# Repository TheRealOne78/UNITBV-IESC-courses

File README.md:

# UNITBV-IESC-courses

## ROMÂNĂ / ROMANIAN

Acest depozit git servește drept caietul meu digital personal pentru toate orele pe care le-am urmat la facultatea de _Inginerie Electrică și Știința Calculatoarelor_ din UniTBv (Universitatea Transilvania din Brașov). Chiar dacă vizibilitatea acestui depozit este setată la vizualizare publică (acces mai ușor pentru mine), toate fișierele și conținutul lor sunt protejate în mare măsură de drepturi de autor fie de către UniTBv sau de către alți terți care pot avea sau nu o relație cu UniTBv.

Cu toate acestea, bibliografia este disponibilă pe fiecare fișier `README.md` pentru fiecare clasă, așa cum este furnizată de UniTBv. Dacă sunteți deținătorul drepturilor de autor și nu puteți găsi creditele necesare în secțiunile de bibliografie, vă rog să-mi trimiteți un E-Mail la <a href="elias.bajcsi@student.unitbv.ro">elias.bajcsi@student.unitbv.ro</a> deoarece toate _Pull requests_ și _Issues_ vor fi ignorate.

## ENGLEZĂ / ENGLISH

This git repository serves as my personal digital notebook for all classes I attended to the _Electrical Engineering and Computer Science_ college at UniTBv (Transilvania University of Brașov). Even though this repository's visibility is set to public view (easier access for myself), all the files and their contents are heavily copyrighted either by UniTBv or third parties that may or may not have a relation with UniTBv.

However, bibliography is available on every `README.md` file for every class, as provided by UniTBv. If you are a copyright holder and you can't find the necessary credits in the bibliography sections, please send me an E-Mail to <a href="elias.bajcsi@student.unitbv.ro">elias.bajcsi@student.unitbv.ro</a> as all _Pull requests_ and _Issues_ will be ignored.

### Grupa/Group: 4LF731

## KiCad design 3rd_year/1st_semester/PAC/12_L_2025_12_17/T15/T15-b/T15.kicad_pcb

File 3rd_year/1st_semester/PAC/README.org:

#+TITLE: Proiectarea asistată de calculator a modulelor electronice [PAC]

Profesor de curs: PANĂ Gheorghe
Profesor de laborator: PANĂ Gheorghe

An III, 2025-2026 Semestrul I

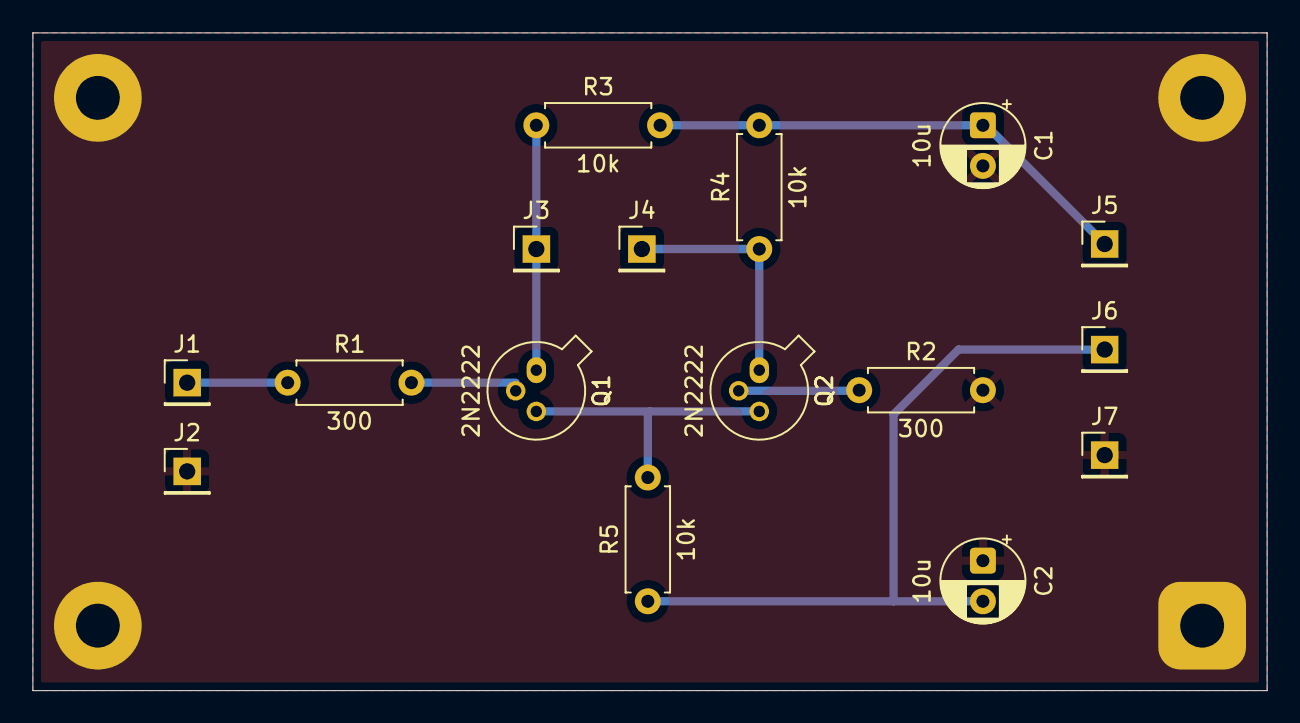
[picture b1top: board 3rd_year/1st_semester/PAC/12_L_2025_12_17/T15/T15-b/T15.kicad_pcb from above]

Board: 2 copper layers, 76.0 x 40.5 mm, 20 parts (0 on the bottom side), 9 nets.

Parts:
C1, C2: 10u; CP_Radial_D5.0mm_P2.50mm
J1, J2, J3, J4, J5, J6, J7: Conn_01x01; PinHeader_1x01_P2.54mm_Vertical
Q1, Q2: 2N2222; TO-18-3
R1, R2: 300; R_Axial_DIN0207_L6.3mm_D2.5mm_P7.62mm_Horizontal
R3, R4, R5: 10k; R_Axial_DIN0207_L6.3mm_D2.5mm_P7.62mm_Horizontal
REF1, REF2, REF3, REF4: MountingHole_2.7mm_Pad

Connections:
0: C1.2, C2.1, J2.1, J7.1, R2.2, REF1.1, REF2.1, REF3.1, REF4.1
/V+: C1.1, J5.1, R3.2, R4.2
/V-: C2.2, J6.1, R5.1
/out1: J3.1, Q1.1 (C), R3.1
/out2: J4.1, Q2.1 (C), R4.1
unnamed: J1.1, R1.1
unnamed: Q1.2 (B), R1.2
unnamed: Q1.3 (E), Q2.3 (E), R5.2
unnamed: Q2.2 (B), R2.1

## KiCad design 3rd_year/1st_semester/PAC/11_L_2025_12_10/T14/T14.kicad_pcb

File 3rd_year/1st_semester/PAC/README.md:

## PAC - Proiectarea Asistată de Calculator a modulelor electronice

Profesor de curs:
Profesor de seminar:
Profesor de laborator:
Profesor de proiect:

An III, 2025-2026 Semestrul I

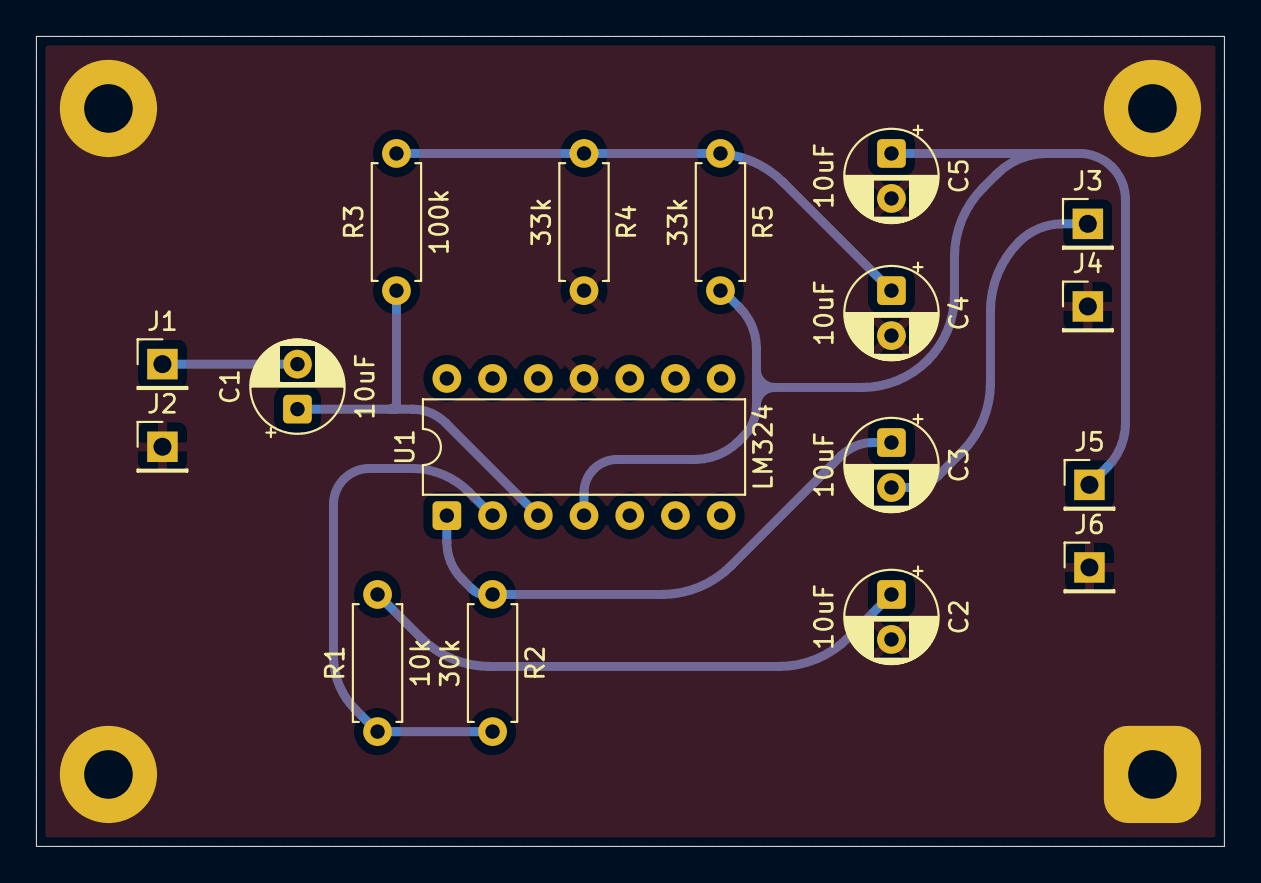
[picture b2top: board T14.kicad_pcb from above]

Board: 2 copper layers, 66.0 x 45.0 mm, 21 parts (0 on the bottom side), 9 nets.

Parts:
C1, C2, C3, C4, C5: 10uF; CP_Radial_D5.0mm_P2.50mm
J1, J2, J3, J4, J5, J6: Conn_01x01; PinHeader_1x01_P2.54mm_Vertical
R1: 10k; R_Axial_DIN0207_L6.3mm_D2.5mm_P7.62mm_Horizontal
R2: 30k; R_Axial_DIN0207_L6.3mm_D2.5mm_P7.62mm_Horizontal
R3: 100k; R_Axial_DIN0207_L6.3mm_D2.5mm_P7.62mm_Horizontal
R4, R5: 33k; R_Axial_DIN0207_L6.3mm_D2.5mm_P7.62mm_Horizontal
REF1, REF2, REF3, REF4: MountingHole_2.7mm_Pad
U1: LM324; DIP-14_W7.62mm

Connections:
0: C2.2, C4.2, C5.2, J2.1, J4.1, J6.1, R4.2, REF1.1, REF2.1, REF3.1, REF4.1, U1.11 (V-)
unnamed: C2.1, R1.2
unnamed: C3.1, R2.1, U1.1
unnamed: C4.1, R3.2, R4.1, R5.1
unnamed: C1.2, J1.1
unnamed: C3.2, J3.1
unnamed: C5.1, J5.1, R5.2, U1.4 (V+)
unnamed: C1.1, R3.1, U1.3 (+)
unnamed: R1.1, R2.2, U1.2 (-)

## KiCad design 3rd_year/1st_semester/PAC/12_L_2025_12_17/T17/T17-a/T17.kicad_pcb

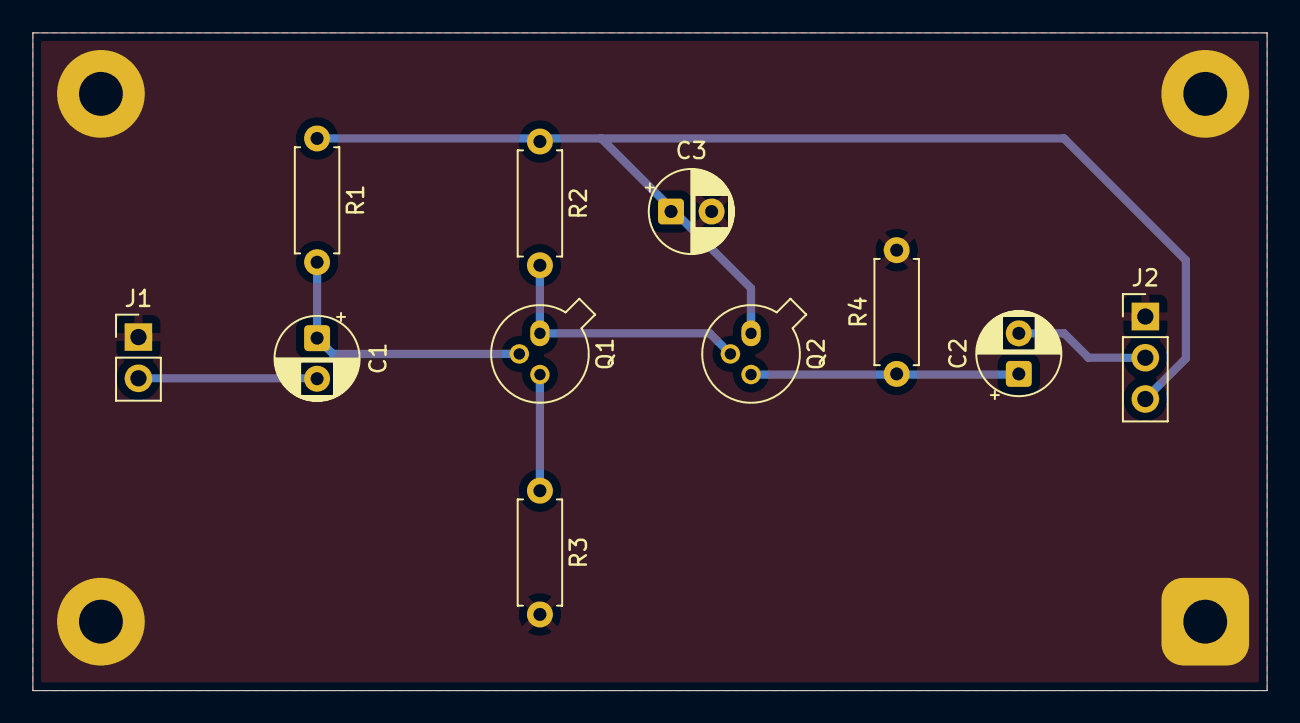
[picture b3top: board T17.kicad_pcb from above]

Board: 2 copper layers, 76.0 x 40.5 mm, 15 parts (0 on the bottom side), 8 nets.

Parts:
C1, C2, C3: 10u; CP_Radial_D5.0mm_P2.50mm
J1: Conn_01x02; PinHeader_1x02_P2.54mm_Vertical
J2: Conn_01x03; PinHeader_1x03_P2.54mm_Vertical
Q1, Q2: 2N2222; TO-18-3
R1: 1Meg; R_Axial_DIN0207_L6.3mm_D2.5mm_P7.62mm_Horizontal
R2: 5.1k; R_Axial_DIN0207_L6.3mm_D2.5mm_P7.62mm_Horizontal
R3, R4: 1k; R_Axial_DIN0207_L6.3mm_D2.5mm_P7.62mm_Horizontal
REF1, REF2, REF3, REF4: MountingHole_2.7mm_Pad

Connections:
0: C3.2, J1.1, J2.1, R3.2, R4.2, REF1.1, REF2.1, REF3.1, REF4.1
/+12V: C3.1, J2.3, Q2.1 (C), R1.1, R2.1
/out: C2.2, J2.2
unnamed: C1.2, J1.2
unnamed: C1.1, Q1.2 (B), R1.2
unnamed: Q1.1 (C), Q2.2 (B), R2.2
unnamed: Q1.3 (E), R3.1
unnamed: C2.1, Q2.3 (E), R4.1

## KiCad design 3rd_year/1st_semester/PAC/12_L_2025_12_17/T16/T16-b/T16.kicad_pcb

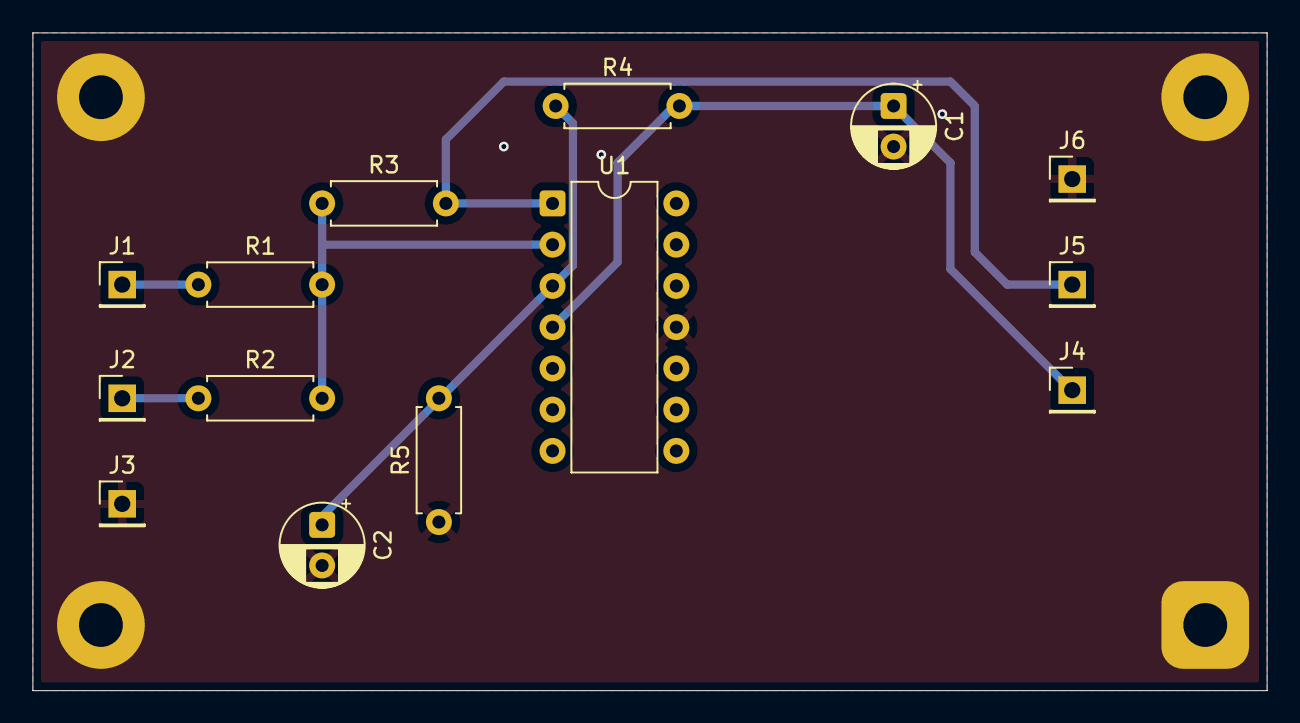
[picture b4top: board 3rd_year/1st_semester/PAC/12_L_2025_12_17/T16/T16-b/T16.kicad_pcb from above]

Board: 2 copper layers, 76.0 x 40.5 mm, 18 parts (0 on the bottom side), 7 nets.

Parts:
C1, C2: 10u; CP_Radial_D5.0mm_P2.50mm
J1, J2, J3, J4, J5, J6: Conn_01x01; PinHeader_1x01_P2.54mm_Vertical
R1: 10k; R_Axial_DIN0207_L6.3mm_D2.5mm_P7.62mm_Horizontal
R2, R3: 30k; R_Axial_DIN0207_L6.3mm_D2.5mm_P7.62mm_Horizontal
R4, R5: 20k; R_Axial_DIN0207_L6.3mm_D2.5mm_P7.62mm_Horizontal
REF1, REF2, REF3, REF4: MountingHole_2.7mm_Pad
U1: LM324; DIP-14_W7.62mm

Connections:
0: C1.2, C2.2, J3.1, J6.1, R5.1, REF1.1, REF2.1, REF3.1, REF4.1, U1.11 (V-)
unnamed: J1.1, R1.1
unnamed: J2.1, R2.1
unnamed: J5.1, R3.2, U1.1
unnamed: C2.1, R4.1, R5.2, U1.3 (+)
unnamed: R1.2, R2.2, R3.1, U1.2 (-)
V+: C1.1, J4.1, R4.2, U1.4 (V+)

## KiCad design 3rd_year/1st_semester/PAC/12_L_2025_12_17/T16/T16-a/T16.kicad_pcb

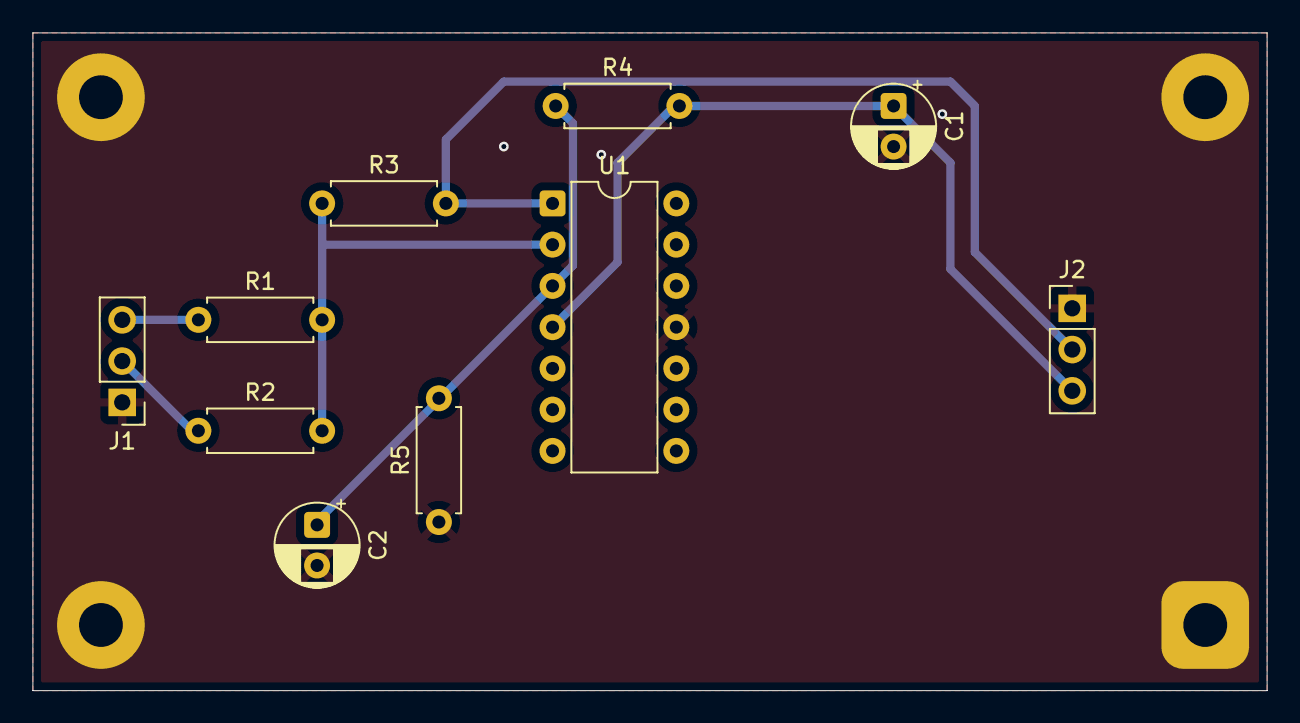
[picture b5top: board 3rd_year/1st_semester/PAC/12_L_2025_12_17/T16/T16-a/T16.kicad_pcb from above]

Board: 2 copper layers, 76.0 x 40.5 mm, 14 parts (0 on the bottom side), 7 nets.

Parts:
C1, C2: 10u; CP_Radial_D5.0mm_P2.50mm
J1, J2: Conn_01x03; PinHeader_1x03_P2.54mm_Vertical
R1: 10k; R_Axial_DIN0207_L6.3mm_D2.5mm_P7.62mm_Horizontal
R2, R3: 30k; R_Axial_DIN0207_L6.3mm_D2.5mm_P7.62mm_Horizontal
R4, R5: 20k; R_Axial_DIN0207_L6.3mm_D2.5mm_P7.62mm_Horizontal
REF1, REF2, REF3, REF4: MountingHole_2.7mm_Pad
U1: LM324; DIP-14_W7.62mm

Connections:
0: C1.2, C2.2, J1.1, J2.1, R5.1, REF1.1, REF2.1, REF3.1, REF4.1, U1.11 (V-)
unnamed: J1.2, R2.1
unnamed: J1.3, R1.1
unnamed: J2.2, R3.2, U1.1
unnamed: C2.1, R4.1, R5.2, U1.3 (+)
unnamed: R1.2, R2.2, R3.1, U1.2 (-)
V+: C1.1, J2.3, R4.2, U1.4 (V+)

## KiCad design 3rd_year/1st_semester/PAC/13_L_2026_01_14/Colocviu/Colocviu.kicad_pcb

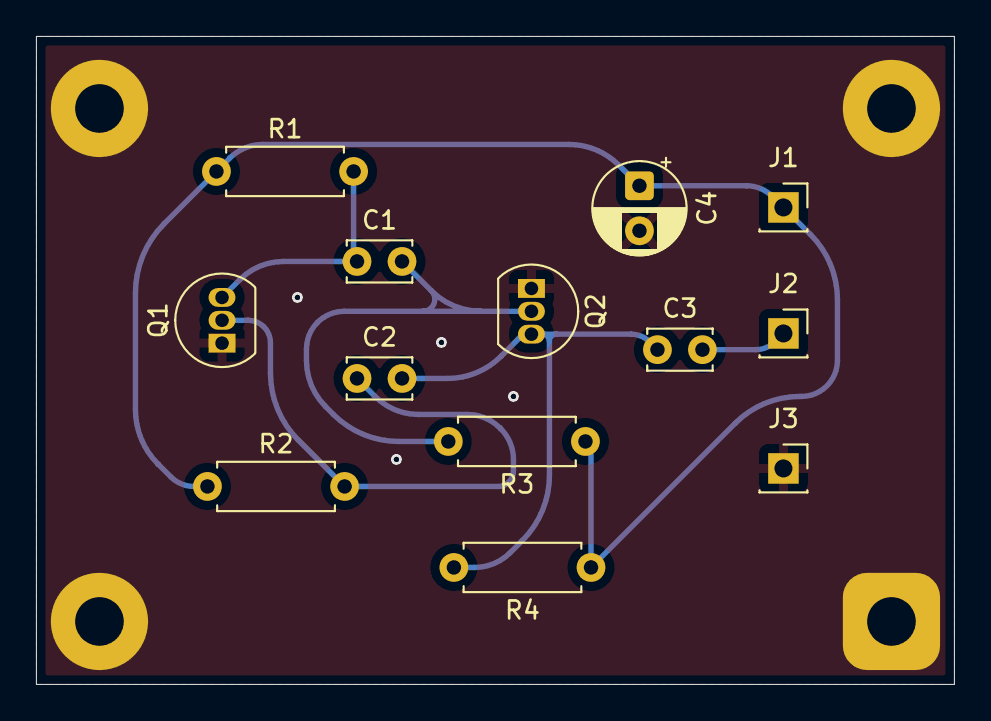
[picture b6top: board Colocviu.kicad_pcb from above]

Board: 2 copper layers, 51.0 x 36.0 mm, 17 parts (0 on the bottom side), 7 nets.

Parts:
C1, C2, C3: 100n; C_Disc_D3.4mm_W2.1mm_P2.50mm
C4: 10uF; CP_Radial_D5.0mm_P2.50mm
J1, J2, J3: Conn_01x01; PinSocket_1x01_P2.54mm_Vertical
Q1, Q2: 2N3904; TO-92_Inline
R1, R4: 2.2k; R_Axial_DIN0207_L6.3mm_D2.5mm_P7.62mm_Horizontal
R2, R3: 33k; R_Axial_DIN0207_L6.3mm_D2.5mm_P7.62mm_Horizontal
REF1, REF2, REF3, REF4: MountingHole_2.7mm_Pad

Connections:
0: C4.2, J3.1, Q1.1 (E), Q2.1 (E), REF1.1, REF2.1, REF3.1, REF4.1
unnamed: C4.1, J1.1, R1.1, R2.1, R3.1, R4.1
unnamed: C3.2, J2.1
unnamed: C2.1, Q1.2 (B), R2.2
unnamed: C1.1, Q1.3 (C), R1.2
unnamed: C1.2, Q2.2 (B), R3.2
unnamed: C2.2, C3.1, Q2.3 (C), R4.2

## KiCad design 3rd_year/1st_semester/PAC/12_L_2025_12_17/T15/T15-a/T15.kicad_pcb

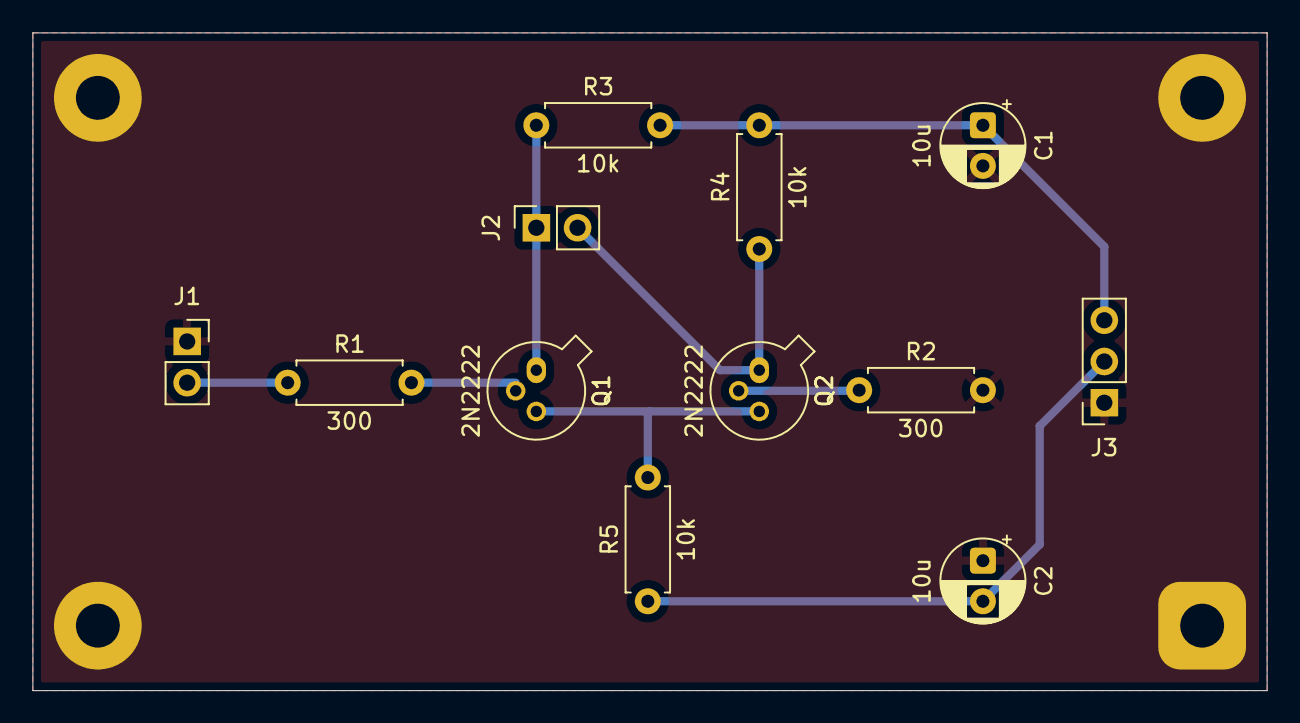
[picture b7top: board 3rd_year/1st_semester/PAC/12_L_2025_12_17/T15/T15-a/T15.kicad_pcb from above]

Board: 2 copper layers, 76.0 x 40.5 mm, 16 parts (0 on the bottom side), 9 nets.

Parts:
C1, C2: 10u; CP_Radial_D5.0mm_P2.50mm
J1, J2: Conn_01x02; PinSocket_1x02_P2.54mm_Vertical
J3: Conn_01x03; PinSocket_1x03_P2.54mm_Vertical
Q1, Q2: 2N2222; TO-18-3
R1, R2: 300; R_Axial_DIN0207_L6.3mm_D2.5mm_P7.62mm_Horizontal
R3, R4, R5: 10k; R_Axial_DIN0207_L6.3mm_D2.5mm_P7.62mm_Horizontal
REF1, REF2, REF3, REF4: MountingHole_2.7mm_Pad

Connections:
0: C1.2, C2.1, J1.1, J3.1, R2.2, REF1.1, REF2.1, REF3.1, REF4.1
/V+: C1.1, J3.3, R3.2, R4.2
/V-: C2.2, J3.2, R5.1
unnamed: J1.2, R1.1
unnamed: J2.1, Q1.1 (C), R3.1
unnamed: J2.2, Q2.1 (C), R4.1
unnamed: Q1.2 (B), R1.2
unnamed: Q1.3 (E), Q2.3 (E), R5.2
unnamed: Q2.2 (B), R2.1

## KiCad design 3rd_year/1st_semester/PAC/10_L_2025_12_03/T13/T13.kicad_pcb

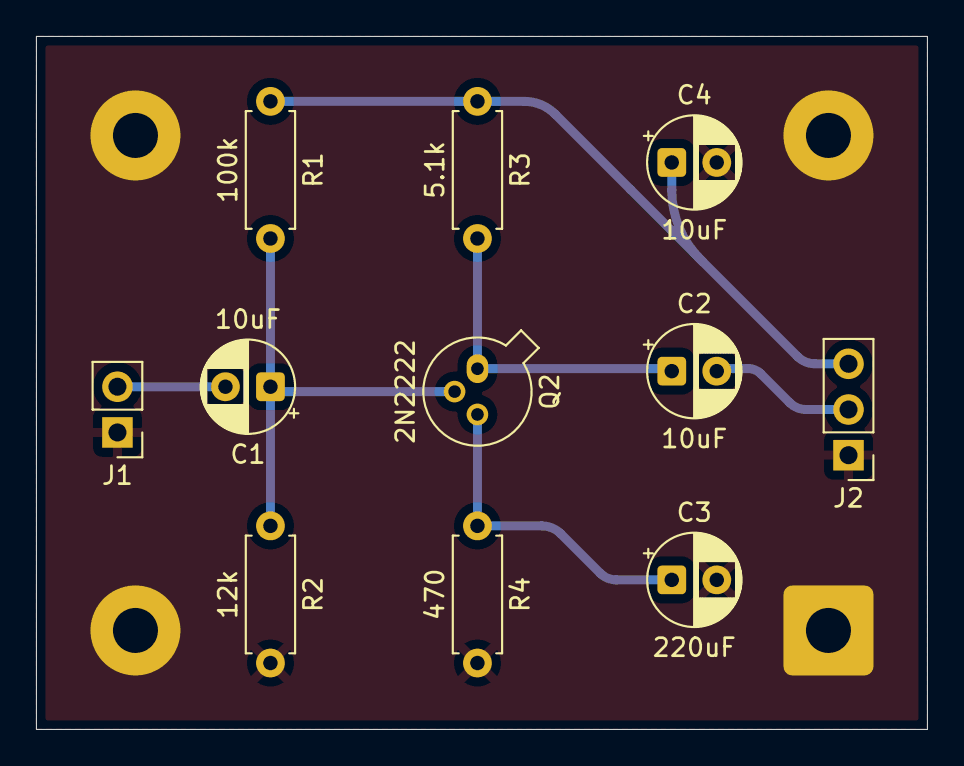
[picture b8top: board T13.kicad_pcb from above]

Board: 2 copper layers, 49.5 x 38.5 mm, 15 parts (0 on the bottom side), 7 nets.

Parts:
C1, C2, C4: 10uF; CP_Radial_D5.0mm_P2.50mm
C3: 220uF; CP_Radial_D5.0mm_P2.50mm
J1: Conn_01x02; PinHeader_1x02_P2.54mm_Vertical
J2: Conn_01x03; PinHeader_1x03_P2.54mm_Vertical
Q2: 2N2222; TO-18-3
R1: 100k; R_Axial_DIN0207_L6.3mm_D2.5mm_P7.62mm_Horizontal
R2: 12k; R_Axial_DIN0207_L6.3mm_D2.5mm_P7.62mm_Horizontal
R3: 5.1k; R_Axial_DIN0207_L6.3mm_D2.5mm_P7.62mm_Horizontal
R4: 470; R_Axial_DIN0207_L6.3mm_D2.5mm_P7.62mm_Horizontal
REF0, REF1, REF2, REF3: MountingHole_2.5mm_Pad

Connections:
0: C3.2, C4.2, J1.1, J2.1, R2.2, R4.2, REF0.1, REF1.1, REF2.1, REF3.1
unnamed: C1.2, J1.2
unnamed: C2.2, J2.2
unnamed: C4.1, J2.3, R1.1, R3.1
unnamed: C1.1, Q2.2 (B), R1.2, R2.1
unnamed: C2.1, Q2.1 (C), R3.2
unnamed: C3.1, Q2.3 (E), R4.1

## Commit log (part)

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2023-10-11 InfoAp/1-l-2023-10-11/
    remove accidental README.html compilation
2023-10-11 InfoAp/README.md
2023-10-11 fix typo on /README.md
2023-10-12 ALGAD/2-c-2023-10-06
2023-10-13 Engleza/1_C_2023_10_13/
2023-10-13 Comunicare/1-s-2023-10-09
2023-10-13 fix minor org mode designs
2023-10-14 complete ALGAD/2-c-2023-10-06
2023-10-15 AnMate/1-s-2023-10-03
2023-10-16 Comunicare/2-t-2023-10-10
2023-10-16 Comunicare/3-s-2023-10-16
2023-10-17 AnMate/3-s-2023-10-10 alpha stage
2023-10-17 update PCLP1
2023-10-17 [ALPHA] AnMate/2-c-2023-10-06
2023-10-17 [ALPHA] AnMate/4-c-2023-10-14
2023-10-17 [ALPHA] 5-c-2023-10-16/README.md
2023-10-17 [ALPHA] 3-s-2023-10-10/README.md
2023-10-18 InfoAp/2-l-2023-10-18
2023-10-18 [ALPHA] AnMate/3-s-2023-10-10
2023-10-19 Engleza/2_S_2023_10_19
2023-10-19 PCLP1/4-L-2023-10-19
2023-10-21 [ALPHA] (Poze + PDF) AnMate/6-c-2023-10-20
2023-10-21 [ALPHA] (poze) ALGAD/5-c-2023-10-20
2023-10-21 merge
2023-10-21 AnMate/3-s-2023-10-10
2023-10-22 AnMate/5-s-2023-10-17
2023-10-22 add scanned images to AnMate/1-s-2023-10-03
2023-10-22 add scanned images to AnMate/3-s-2023-10-10
2023-10-22 add scanned images to AnMate/4-c-2023-10-14
2023-10-22 add scanned images to AnMate/5-s-2023-10-17
2023-10-25 InfoAp/3-l-2023-10-25
2023-10-27 PCLP1/6-L-2023-10-26
2023-10-27 [ALPHA] Engleza/3_C_2023_10_27
2023-10-30 add derivatives table
2023-10-30 Comunicare/5-s-2023-10-30
2023-10-30 ignore Psiho-Pedagogie directory
2023-11-01 InfoAp/4-l-2023-11-01
2023-11-02 AnMate: Rename Misc to 9999_Misc and add copyright Engleza: Add 9999_Misc with copyright PCLP1/8_l_2023_11_02
2023-11-06 AnMate/7-S-2023-10-24
2023-11-06 AnMate/8-C-2023-10-27
2023-11-06 AnMate/9-S-2023-10-31
2023-11-06 AnMate/10-C-2023-11-03
2023-11-06 [ALPHA] ALGAD/9-C-2023-11-0
2023-11-08 InfoAp/5-l-2023-11-08
2023-11-09 PCLP1/10-l-2023-11-09
2023-11-09 remove accidental binary files in /PCLP1/8_l_2023_11_02/src
2023-11-09 ALGAD/1-S-2023-10-04
2023-11-09 AnMate/11_S_2023_11_07
2023-11-09 ALGAD/10_S_2023_11_08
2023-11-09 ALGAD/2-C-2023-10-06/ ALGAD/3-S-2023-10-11/ ALGAD/4-C-2023-10-13/ ALGAD/5-C-2023-10-20/ ALGAD/6-S-2023-10-25/ ALGAD/7-C-2023-10-27/ ALGAD/8-S-2023-11-01/
2023-11-10 Engleza/5-C-2023-11-10
2023-11-10 ALGAD/11_C_2023_11_10
2023-11-10 rename temp.pdf to Scan.pdf for accidental reasons
2023-11-10 AnMate/12-C-2023-11-10/ renamed: AnMate/11_S_2023_11_07/ -> AnMate/11-S-2023-11-07/
2023-11-13 Comunicare: Prezentare Ada Lovelace
2023-11-15 InfoAp/6-l-2023-11-15
2023-11-16 Engleza/6-S-2023-11-16/ Add README.md to Engleza/4_S_2023_11_02/
2023-11-16 PCLP1/12-l-2023-11-16/
2023-11-22 replace imag.pub.ro domain with the new vega.unitbv.ro domain for copyright in README.md
2023-11-23 InfoAp/7-l-2023-11-22
2023-11-24 ALGAD
2023-11-24 AnMate/13_S_2023_11_14
2023-11-24 AnMate
2023-11-24 Engleza/7-C-2023-11-24
2023-12-05 AnMate/18_S_2023_12_05
2023-12-16 hello world
2023-12-26 PCLP1 tema 2
2023-12-27 PCLP1 tema_2: reduce code size
2024-01-10 InfoAP
2024-01-20 Engleza
2024-01-22 [COMUNICARE] Misc stuff
2024-03-08 refactor file structure for first semester
2024-03-08 PCLP2/04_L_2024_03_06
2024-03-08 PCLP2/01_P_2024_02_20
2024-03-08 [PCLP2] add README.md
2024-03-08 [PCLP2] fix markdown formatting
2024-03-08 [Engleza] Add 'README.md's
2024-03-08 [PCLP2/Project] Add project submodule
2024-03-08 remove accidental .gitmodules file
2024-03-13 PCLP2/07_L_2024_03_13
2024-03-13 Engleza/03_S_2024_03_13
2024-03-19 Engleza/04_C_2024_03_15
2024-03-19 PCLP2/09_L_2024_03_19
2024-03-19 fix minor spelling issue
2024-03-19 Add Fizica class
2024-03-22 fix SERVER_SHUTDOWN NTFY formatting
2024-03-23 Add Electro-Tehnica
2024-03-23 add TPSM
2024-03-23 Add Matematici Speciale
2024-03-23 [FIZICA Lab] Add blackboard content
2024-03-25 Update Electro-Tehnica
2024-03-26 Update PCLP2/09_L_2024_03_19
2024-03-27 Matematici_Speciale/11_C_2024_03_25
2024-03-27 Engleza/05_S_2024_03_27
2024-03-27 PCLP2/13_L_2024_03_26
2024-03-28 PCLP2/14_C_2024_03_28
2024-04-10 PCLP2/17_L_2024_04_10
2024-04-16 PCLP2/Tema_1
2024-04-17 Add Electro-Tehnica files
2024-04-23 PCLP2/20_L_2024_04_23
2024-04-29 Add ET and Fizica
2024-05-05 Fizica/20_L_2024_04_16
2024-05-08 Fizica/15_L_2024_04_02
2024-05-14 PCLP2/22_L_2024_05_14
    Rebase
2024-05-14 rebase
2024-05-17 PCLP2/Tema_2
2024-05-17 PCLP2/Tema_2 - use CXX instead of C for Makefile
2024-05-29 update commits TTUYDM
2024-10-25 commit some stuff
2024-10-25 add unstaged files
2024-10-26 get jdtls to work
2024-10-31 finally get Emacs to work with Gradle (for real this time)
2024-10-31 remove accidentally comited Java bytecode
2024-11-07 restructure
2024-11-07 Remove accidentally commited file
2024-11-07 solve lab
2024-11-10 upload prototype
2024-11-21 add java
2024-11-22 add springboot submodule
2024-12-05 idfk
2024-12-22 commit new TTUYDM commits
2024-12-22 commit unstaged files
2024-12-24 i don't fucking know, don't fucking ask me for fuck's sake!
2024-12-28 add DPPD project
2025-01-03 add a shitton load of shit I don't remember what it does anymore
2025-01-04 AAAAAAAAAAAAAAAAAAAAAAAAAAAAAAAAAAAAAAAAAAAAAAAAAAAAAAAAAAAAAAAAAAAAAAAAAAAAAAAAAAAAAAAAAAAAAAAAAAAAAAAAAAAAAAAAAAAAAAAAAAAAAAAAAAAAAAAAAAAAAAAAAAAAAAAAAAAAAAA
2025-01-05 Complete the lab project
2025-01-05 commit project
2025-01-05 add portofoliu DPPD
2025-01-05 Add ME labs
2025-01-12 [Java project] fuck it, as long as it works, it will do
2025-02-06 add exercise
2025-03-13 add new sester stuff
2025-03-13 add more second semester stuff
2025-03-14 add more new semester stuff
2025-03-16 [PIU] 06_L_2025_03_11 - Homework
2025-03-24 ED add PDF for hw
2025-04-03 commit progress
2025-05-04 add some untracked scanned files
2025-05-24 [PC] Add solved labs
2025-05-27 PIU - colocviu 3
2025-05-29 DPPD
2025-07-19 commit uncommited changes
2025-08-20 Add scans of companies
2025-10-02 add stuff
2025-10-02 AMP - 2025.10.02
2025-10-05 add PAC hw and some untracked files
    remove duplicate file
2025-10-06 init 3rd_yr/1st_sem
2025-10-06 Add seminar files
    Modified-by: TheRealOne78 <bajcsielias78@gmail.com>
    Modified-by: TheRealOne78 <bajcsielias78@gmail.com>
2025-10-10 Commit unstaged
2025-10-23 commit uncommited
2025-10-26 IV+IA
2025-10-30 commit uncommited stuff
2025-11-10 uncommited
2025-11-10 fix lab
2025-11-10 fix uncommited
2025-11-21 tema 1 IA
2025-12-05 HW 2 AI
2025-12-18 hw AI linear regression
2026-01-07 hw ai
2026-02-20 commit stuff
2026-02-20 SO - decided to also include autgenerated LaTeX and PDF files
2026-02-26 Add IV lectures and add pics for 1st OS lab
2026-03-09 [SO] Finish second lab homework
2026-06-21 cleanup
2026-06-21 Track binary files with Git LFS
